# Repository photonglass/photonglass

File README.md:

日本語 | [English](README.en.md)

# PHOTON GLASS

一人称のカメラで捉えるイメージから，音などのフィードバックでユーザーにインタラクションする，メガネ型のデバイス〈PHOTON GLASS〉のハードウェアデータです。
PHOTON GLASS は、文字を読み上げるメガネOTON GLASS ver5 を元にしながら、自作の容易さや改変性を高め、ツールキットとして新しく開発したものです。
基板2枚（メイン基板・カメラ基板）の設計データ、3Dプリンターで造形できる本体とカメラユニットの筐体、電源ケーブルのカバー、本体のプログラム、組み立てとセットアップの手順を公開しています。
ここで公開しているプログラムは、PHOTON GLASS のサンプル実装のひとつです。一人称カメラで捉えた文字を読み上げる（画像から文字を認識し、音声で読み上げる）機能を実行します。

## 中身

| フォルダ | 内容 | 開けるソフト |
|---|---|---|
| [`hardware/`](hardware/README.md) | 基板2枚の概要、ファイルの開き方、元設計からの変更 | — |
| [`hardware/main-board/`](hardware/main-board) | メイン基板（Raspberry Pi Zero 2 W に載る音声・ボタン基板） | KiCad 9 以降 / Fusion（Eagle形式） |
| [`hardware/camera-board/`](hardware/camera-board) | カメラ基板（HDMIケーブルでメイン基板とつながる） | KiCad 9 以降 / Fusion（Eagle形式） |
| [`enclosure/main-body/`](enclosure/main-body) | 本体の筐体（ボディ前面・背面・側面、メインボタン、サブボタン、状態ランプのレンズ） | F3D（Fusion）/ STEP（FreeCAD など）/ STL・3MF（スライサー） |
| [`enclosure/camera-unit/`](enclosure/camera-unit) | カメラユニットの筐体・メガネ用アタッチメント | STEP（Fusion・FreeCAD など）/ STL・3MF（スライサー）/ Python（CadQuery） |
| [`enclosure/usb-power-cable/`](enclosure/usb-power-cable) | モバイルバッテリーからメイン基板へ給電するケーブルの作り方（配線・部品）と、USB プラグのカバー | STEP / STL / Python（CadQuery） |
| [`software/`](software) | 本体プログラムと効果音。普段使うのは `main_async.py`、仕組みを学ぶなら流れの読みやすい `main_seq.py`（違いは [`software/README.md`](software/README.md)） | Python 3（Raspberry Pi） |
| [`software/test/`](software/test) | 組み立て後の動作テスト用スクリプト（Raspberry Pi で実行） | Python 3 |
| [`docs/`](docs) | 組み立てガイド（[`BUILD_GUIDE.md`](docs/BUILD_GUIDE.md)）、Raspberry Pi のセットアップ（[`SETUP_RASPBERRY_PI.md`](docs/SETUP_RASPBERRY_PI.md)）、部品リスト（[`parts_list.md`](docs/parts_list.md)：データシート・回路記号の照合結果） | — |

## はじめての人へ
- **まず読む**：[`docs/BUILD_GUIDE.md`](docs/BUILD_GUIDE.md) に、発注から動かすまでの作業の順番と、それぞれで読むドキュメントをまとめています。
- **基板を作る**：[`hardware/JLCPCB_ORDERING.md`](hardware/JLCPCB_ORDERING.md) の手順で、JLCPCB に部品実装まで発注できます（ガーバー・部品表・部品配置ファイル付き）。
- **筐体を印刷する**：本体は [`enclosure/main-body/README.md`](enclosure/main-body/README.md)、カメラユニットは [`enclosure/camera-unit/README.md`](enclosure/camera-unit/README.md) に、印刷設定（Bambu Lab A1 / PETG）と組み立て手順があります。
- **Raspberry Pi を準備する**：[`docs/SETUP_RASPBERRY_PI.md`](docs/SETUP_RASPBERRY_PI.md) に、OS の書き込みから動作テスト、自動起動までの手順があります。
- **設計を変える**：基板は KiCad か Fusion で、筐体は STEP を CAD に読み込んで編集します（本体は Fusion の元データ `.f3d` もあります。カメラユニットと電源ケーブルのカバーは、`src/` の Python スクリプトの数値を変えて作り直すこともできます）。

## 質問・不具合の報告

質問や不具合の報告は、GitHub の Issues で受け付けています。
https://github.com/photonglass/photonglass/issues

## 憲法
PHOTON GLASS の理念と利用、名称、特許については、[憲法（`CHARTER.md`）](CHARTER.md)に定めています。

## ライセンス
Copyright (C) 株式会社オトングラス

対象ごとに、次のライセンスで公開しています。

| 対象 | 含まれるもの | ライセンス | 全文 |
|---|---|---|---|
| ソフトウェア | `software/` のプログラム（`main_async.py`・`main_seq.py`・`test/` など） | GNU General Public License v3.0（GPL-3.0-only） | [`LICENSE`](LICENSE) |
| ハードウェア | `hardware/`（基板の KiCad・Eagle データ、BOM・CPL、ガーバーを作るスクリプト `hardware/tools/gerbgen.py`）、`enclosure/`（筐体の CadQuery スクリプトと設計データ。本体の Fusion の元データ `.f3d` を含む）と、それらの生成物（ガーバー、STL・STEP・3MF）。**例外**：README・写真・画像と `hardware/JLCPCB_ORDERING.md` は除く（ドキュメント・写真・画像として CC BY-SA 4.0） | CERN Open Hardware Licence Version 2 - Strongly Reciprocal（CERN-OHL-S v2） | [`LICENSE-HARDWARE`](LICENSE-HARDWARE) |
| ドキュメント・写真・画像 | `docs/`、`CHARTER.md`、`CONTRIBUTING.md`、各フォルダの `README.md`、`hardware/JLCPCB_ORDERING.md`、Issue のテンプレート（`.github/ISSUE_TEMPLATE/`）、写真・画像（各フォルダの `images/` など） | クリエイティブ・コモンズ 表示-継承 4.0 国際（CC BY-SA 4.0） | 公式テキスト：[日本語](https://creativecommons.org/licenses/by-sa/4.0/legalcode.ja)・[English](https://creativecommons.org/licenses/by-sa/4.0/legalcode.en) |
| サウンド | `software/sound/` の効果音 | CC BY-SA 4.0 | 同上 |

- 各 README、写真・画像、`hardware/JLCPCB_ORDERING.md` は、`hardware/`・`enclosure/`・`software/` の中にあっても CC BY-SA 4.0 です。`software/sound/` も、`software/` の中にありますが CC BY-SA 4.0 です。
- 文書の英語版（`README.en.md`・`CHARTER.en.md`・`hardware/JLCPCB_ORDERING.en.md` など、名前の末尾が `.en.md` のファイル）も、日本語版と同じく CC BY-SA 4.0 です。

### CC BY-SA 4.0 のクレジット表記
ドキュメント・写真・画像・サウンドは、株式会社オトングラスが CC BY-SA 4.0 で提供しています。全文のファイルはこのリポジトリに入れていないので、公式テキスト（[日本語](https://creativecommons.org/licenses/by-sa/4.0/legalcode.ja)・[English](https://creativecommons.org/licenses/by-sa/4.0/legalcode.en)）を見てください。

使うときは、次のようにクレジットを表記してください。改変したときは、改変したことも書いてください。
```
PHOTON GLASS（Copyright (C) 株式会社オトングラス）
https://github.com/photonglass/photonglass
CC BY-SA 4.0 https://creativecommons.org/licenses/by-sa/4.0/
```

### かんたんな説明
正確な条件は、各ライセンスの全文を見てください。

**できること**
- 誰でも無料で、このデータで基板や筐体を作り、使い、売ることができます。
- 自由に改変できます。

**守ること**
- 作ったもの・改変したものを人に配ったり売ったりするときは、元と同じライセンスで公開する。
  - ソフトウェアとハードウェアは、受け取った人がソース（プログラム・設計データ）を手に入れられるようにする。ハードウェアの場合は、ソースを渡すか、ソースの置き場所を知らせる。
- 著作権表示とライセンスの表示を消さない。改変した場合は、いつ・どこを変えたかを書く。
- ドキュメント・写真・画像・サウンドを使うときは、上のクレジットを表記する。

**その他**
- 無保証です（作ったものが動かなくても、作者は責任を負いません）。
- 自分で使うだけなら、改変したデータを公開する義務はありません。
- 特許の扱いは、憲法の[「3. 特許について」](CHARTER.md#3-特許について)を見てください。

### 商用ライセンス
クローズドな製品への組み込みなど、各ライセンスの条件と異なる利用を希望する場合は、商用ライセンスを個別に契約できます。問い合わせはこちら：https://note.com/keisukeshimakage/n/nef3c9957ae25

### 含まれていないもの
- 部品メーカーや EasyEDA/LCSC が配布している部品の3Dモデル（再配布の条件がはっきりしないため）。基板の3D形状は KiCad や Fusion の3Dビューで確認してください。
- Google Cloud の API キー（各自で用意して、プログラムと同じフォルダの `api_key.txt` に書く。書き方は [`software/README.md`](software/README.md#動かし方)）。

### クレジット
**PHOTON GLASS（2026年）**
- 回路・基板設計、ドキュメンテーション：山中将治（Masaharu Yamanaka）
- プロダクトデザイン：小松靖知（Yasutomo Komatsu）
- プログラミング：石塚日向（Hinata Ishizuka）
- アドバイジング：須田拓也（Hiroya Suda）、高橋卓久真（Takuma Takahashi）、陳冠宇（Chen Kuan-Yu）

**OTON GLASS ver5（2019年）― PHOTON GLASSの元となったモデル**
- エンジニアリング：宮下恵太（Keita Miyashita）
- サーバーサイドエンジニアリング：鶴岡秀樹（Hideki Tsuruoka）
- プロダクトデザイン：佐野友優（Tomomasa Sano）
- サウンドデザイン：田中堅大（Kenta Tanaka）

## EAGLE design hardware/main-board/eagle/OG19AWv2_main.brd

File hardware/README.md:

日本語 | [English](README.en.md)

# 基板 / Boards

| 基板 | 役割 | 大きさ |
|---|---|---|
| [`main-board/`](main-board) OG19AWv2 | Raspberry Pi Zero 2 W の40ピンに挿す。音声出力（PCM5102A + PAM8304）、スピーカー用コネクタ、ボタン4個、RGB LED、ヘッドホンジャック、電源用コネクタ（5V）、カメラ基板へのHDMI | 79 × 42 mm、2層 |
| [`camera-board/`](camera-board) OG19 PC-3 | カメラユニットの中の基板。カメラ（Adafruit 3508 Zero Spy Camera、標準レンズ版。[`enclosure/camera-unit` の「必要な部品」](../enclosure/camera-unit/README.md#必要な部品)）をつなぎ、カメラボタン（シャッター）とLEDを載せる。HDMIケーブルでメイン基板へ | 39.3 × 17.2 mm、2層 |

## ファイルの開き方
| ソフト | 開くファイル | 方法 |
|---|---|---|
| **KiCad 9 以降** | `kicad/*.kicad_pro` | ダブルクリックで開く。KiCad 10 で開いて保存すると、ファイルが新しい形式になり KiCad 9 では開けなくなる |
| **Fusion**（旧 Eagle） | `eagle/*.sch` / `*.brd` | Fusion の「ファイル → 開く」で `.sch` を選ぶと、回路図と基板がセットで電子設計として開く |
| Eagle 9.x | `eagle/*.sch` / `*.brd` | そのまま開く（Eagle は 2026年6月に販売とサポートが終了しているので、これから使うなら KiCad か Fusion） |

Eagle・KiCad の部品ライブラリのうち、jst-xh（メイン基板の `5V`・`SPK` のコネクタ）は、yuhki50 氏の [eagle-pcb-library](https://github.com/yuhki50/eagle-pcb-library)（MIT ライセンス）に由来します。

## JLCPCB で作る
各基板のフォルダに、発注に必要なファイル（ガーバー・BOM・CPL）がそろっています。
発注の手順は **[`JLCPCB_ORDERING.md`](JLCPCB_ORDERING.md)** を見てください（基板製造の設定、部品実装の設定、部品の向きの確認、手はんだで付ける部品）。

スピーカー用コネクタの向きは [`main-board/images/speaker_connector_orientation.png`](main-board/images/speaker_connector_orientation.png) を見てください。

## 元設計（OTON GLASS ver5）からの変更
- 在庫のない部品を JLCPCB で買える部品に置き換え（ヘッドホンジャック、RGB LED、ピンソケット、抵抗値の近似など）。詳しくは [`docs/parts_list.md`](../docs/parts_list.md)。
- メイン基板：上辺の段差をなくした、左右の角を対称な面取りにした、HDMI とヘッドホンジャックの前面をそろえた、ボタンを基板の端まで出した、不足していたビアを追加した、など。
- **RGB LED の色と GPIO の対応が変わっています**：GPIO9 = 赤、GPIO11 = 緑、GPIO10 = 青。

## 版の履歴
| 版（シルクの表記） | 変更 |
|---|---|
| メイン基板 `2026 / PB-4`、カメラ基板 `2026 / PC-4` | シルクの名前を「PHOTON GLASS」に変更（前の版はメイン基板「OTONGLASS」、カメラ基板「OTON GLASS」）。メイン基板の表面に、リポジトリの URL（`github.com/photonglass/photonglass`）とライセンス（`CERN-OHL-S v2`）を追加（2026-11-25 に、この文字と「PHOTON GLASS / 2026 / PB-4」を高さ 1.0 mm・線の太さ 0.16 mm に拡大。JLCPCB の最小値は高さ 1.0 mm・線の太さ 0.153 mm）。**銅箔・穴・レジスト・メタルマスク・外形は前の版と同じ**で、変わったのは表面のシルク（`.GTO`）だけ。設計データに残っていた、手はんだ部品（VR1・SW_MAIN・SW_SUB／UP／DOWN）の旧部品の LCSC 番号を外し、実際に使う部品の型番（`MPN`）と購入先（`SUPPLIER`）に置き換え |
| メイン基板 `2019 / PB-3`、カメラ基板 `2019 / PC-3` | 元設計を JLCPCB 向けに直した最初の版（上の「元設計からの変更」） |

カメラ基板は小さく、裏面にも GND のビアが並んでいて URL を入れる場所がないため、URL とライセンスはメイン基板にだけ入れています。

## 組み立て後のテスト
[`software/test/hw_test.py`](../software/test/hw_test.py) を Raspberry Pi で実行すると、LED → ボタン → スピーカー → カメラの順に確認できます。
Raspberry Pi の準備とテストの実行方法は [`docs/SETUP_RASPBERRY_PI.md`](../docs/SETUP_RASPBERRY_PI.md) にあります。

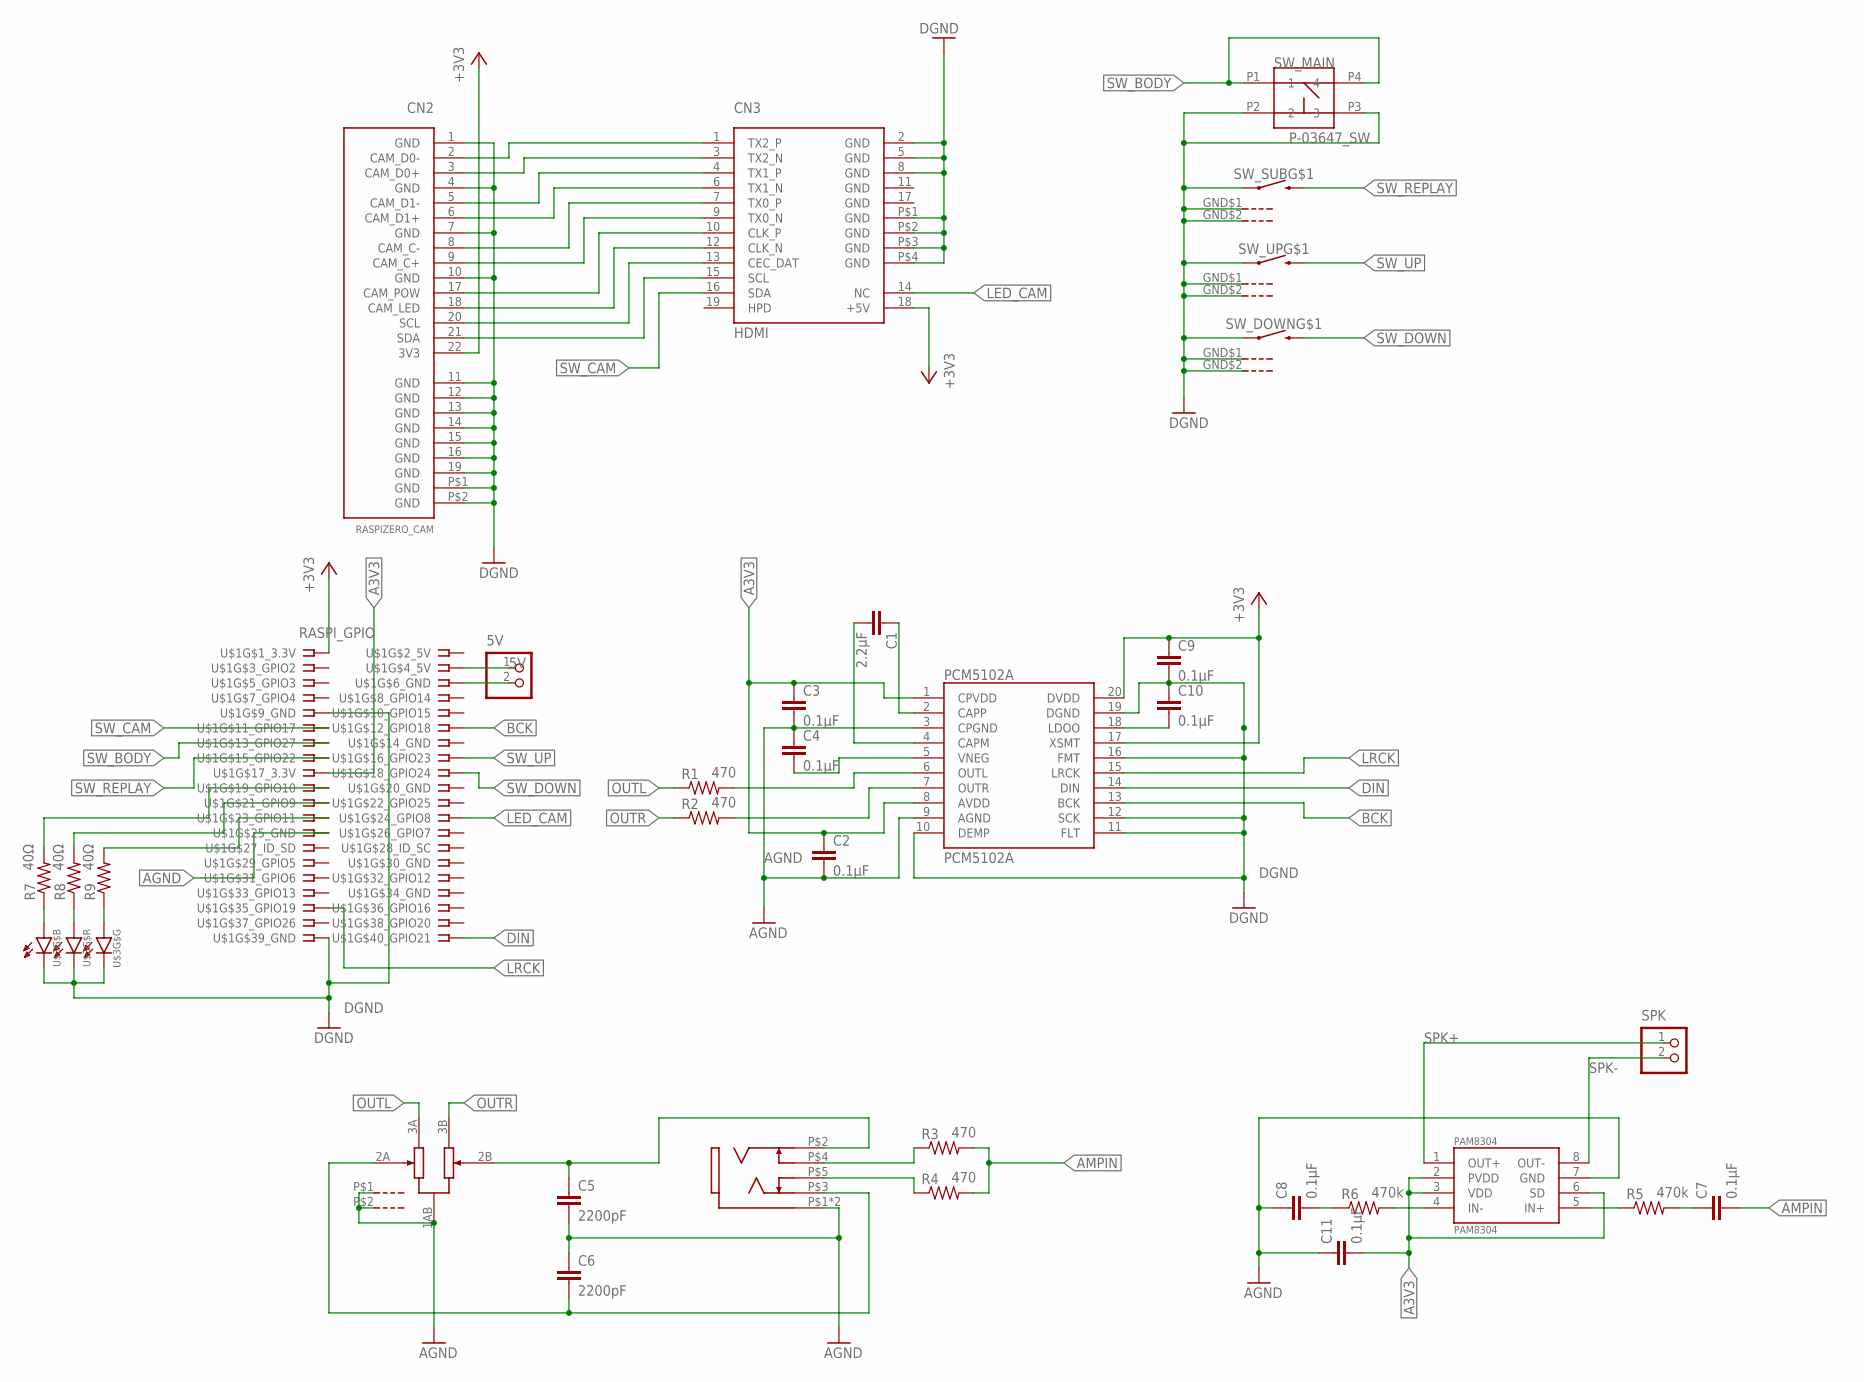
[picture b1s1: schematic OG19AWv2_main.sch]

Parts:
5V: S2B-XH-A; B2B-XH-A; LCSC C158012
C1: 2.2μF; C0603; LCSC C23630
C2, C3, C4, C7, C8, C9, C10, C11: 0.1μF; C0603; LCSC C14663
C5, C6: 2200pF; C0603; LCSC C1604
CN1: SWICHCRAFT_3.5MM_PHONE_JACK; SJ-43516-SMT; LCSC C4992780
CN2: RASPIZERO_CAM; FH12-22S-0.5SH; LCSC C597981
CN3: HDMI; LCSC C427307
PAM8304: PAM8304; MSOP8; LCSC C581342
PCM5102A: PCM5102A; SSOP20; LCSC C107671
R1, R2, R3, R4: 470; R0603; LCSC C23179
R5, R6: 470k; R0603; LCSC C23178
R7, R8, R9: 40Ω; R0603; LCSC C23047
SPK: S2B-XH-A; B2B-XH-A; LCSC C158012
SW_DOWN: ALPS_SKHH_TACT_SWITCH; SKHH_SIDEPUSH; MPN Alps SKHHLPA010
SW_MAIN: P-03647_SW; SW; MPN Cosland TS-0606-F-N-RED
SW_SUB: ALPS_SKHH_TACT_SWITCH; SKHH_SIDEPUSH; MPN Alps SKHHLPA010
SW_UP: ALPS_SKHH_TACT_SWITCH; SKHH_SIDEPUSH; MPN Alps SKHHLPA010
U$1: RASPI_GPIO; SSW-120-02-G-D; LCSC C5124634
U$3: KPF-3236SURKMGKPBC; S6-3528RGBTA; LCSC C2843672
VR1: ALPS_RK10J; RK10J_DIP; MPN R1001G16T2B-B10K

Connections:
5V: 5V.1, U$1.4
+3V3: C9.1, CN2.22 (3V3), CN3.18 (+5V), PCM5102A.17 (XSMT), PCM5102A.20 (DVDD), U$1.1
A3V3: C2.1, C3.1, C11.2, PAM8304.2 (PVDD), PAM8304.3 (VDD), PAM8304.6 (SD), PCM5102A.1 (CPVDD), PCM5102A.8 (AVDD), U$1.17
AGND: C2.2, C3.2, C4.1, C5.2, C6.1, C8.1, C11.1, CN1.P$1, CN1.P$6, PAM8304.7 (GND), PCM5102A.3 (CPGND), PCM5102A.9 (AGND), U$1.25, VR1.1AB, VR1.P$1 (G), VR1.P$2 (G)
AMPIN: C7.2, R3.2, R4.2
BCK: PCM5102A.13 (BCK), U$1.12
DGND: C9.2, C10.1, CN2.1 (GND), CN2.4 (GND), CN2.7 (GND), CN2.10 (GND), CN2.11 (GND), CN2.12 (GND), CN2.13 (GND), CN2.14 (GND), CN2.15 (GND), CN2.16 (GND), CN2.19 (GND), CN2.P$1 (GND), CN2.P$2 (GND), CN3.2 (GND), CN3.5 (GND), CN3.8 (GND), CN3.P$1 (GND), CN3.P$2 (GND), CN3.P$3 (GND), CN3.P$4 (GND), PCM5102A.10 (DEMP), PCM5102A.11 (FLT), PCM5102A.12 (SCK), PCM5102A.16 (FMT), PCM5102A.19 (DGND), SW_DOWN.GND$1 (G), SW_DOWN.GND$2 (G), SW_DOWN.P$1 (1), SW_MAIN.P2 (2), SW_MAIN.P3 (3), SW_SUB.GND$1 (G), SW_SUB.GND$2 (G), SW_SUB.P$1 (1), SW_UP.GND$1 (G), SW_UP.GND$2 (G), SW_UP.P$1 (1), U$1.9, U$1.39, U$3.P$1 (K), U$3.P$2 (K), U$3.P$3 (K)
DIN: PCM5102A.14 (DIN), U$1.40
LED_CAM: CN3.14 (NC), U$1.24
LRCK: PCM5102A.15 (LRCK), U$1.35
unnamed: C5.1, CN1.P$2, VR1.2B
unnamed: C6.2, CN1.P$3, VR1.2A
unnamed: CN1.P$4, R3.1
unnamed: C1.1, PCM5102A.2 (CAPP)
unnamed: C10.2, PCM5102A.18 (LDOO)
unnamed: C1.2, PCM5102A.4 (CAPM)
unnamed: C4.2, PCM5102A.5 (VNEG)
unnamed: CN1.P$5, R4.1
unnamed: PAM8304.5 (IN+), R5.1
unnamed: C7.1, R5.2
unnamed: PAM8304.4 (IN-), R6.2
unnamed: CN2.2 (CAM_D0-), CN3.1 (TX2_P)
unnamed: C8.2, R6.1
unnamed: CN2.3 (CAM_D0+), CN3.3 (TX2_N)
unnamed: CN2.5 (CAM_D1-), CN3.4 (TX1_P)
unnamed: CN2.6 (CAM_D1+), CN3.6 (TX1_N)
unnamed: CN2.8 (CAM_C-), CN3.7 (TX0_P)
unnamed: CN2.9 (CAM_C+), CN3.9 (TX0_N)
unnamed: CN2.17 (CAM_POW), CN3.10 (CLK_P)
unnamed: CN2.18 (CAM_LED), CN3.12 (CLK_N)
unnamed: CN2.20 (SCL), CN3.13 (CEC_DAT)
unnamed: CN2.21 (SDA), CN3.15 (SCL)
unnamed: R7.1, U$3.P$4 (A)
unnamed: 5V.2, U$1.6
unnamed: R7.2, U$1.19
unnamed: R8.2, U$1.21
unnamed: R9.2, U$1.23
unnamed: R8.1, U$3.P$5 (A)
unnamed: R9.1, U$3.P$6 (A)
OUTL: R1.1, VR1.3A
OUTL1: PCM5102A.6 (OUTL), R1.2
OUTR: R2.1, VR1.3B
OUTR1: PCM5102A.7 (OUTR), R2.2
SPK+: PAM8304.1 (OUT+), SPK.1
SPK-: PAM8304.8 (OUT-), SPK.2
SW_BODY: SW_MAIN.P1 (1), SW_MAIN.P4 (4), U$1.13
SW_CAM: CN3.16 (SDA), U$1.11
SW_DOWN: SW_DOWN.P$2 (2), U$1.18
SW_REPLAY: SW_SUB.P$2 (2), U$1.15
SW_UP: SW_UP.P$2 (2), U$1.16

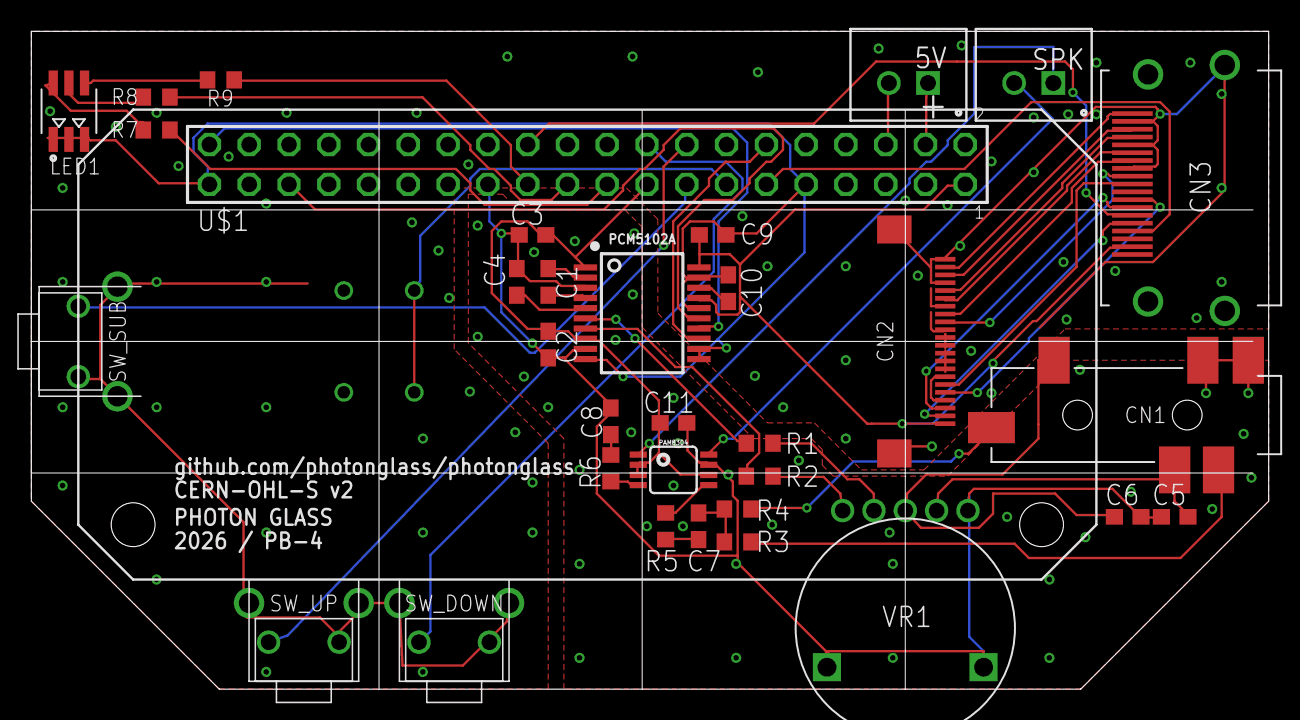
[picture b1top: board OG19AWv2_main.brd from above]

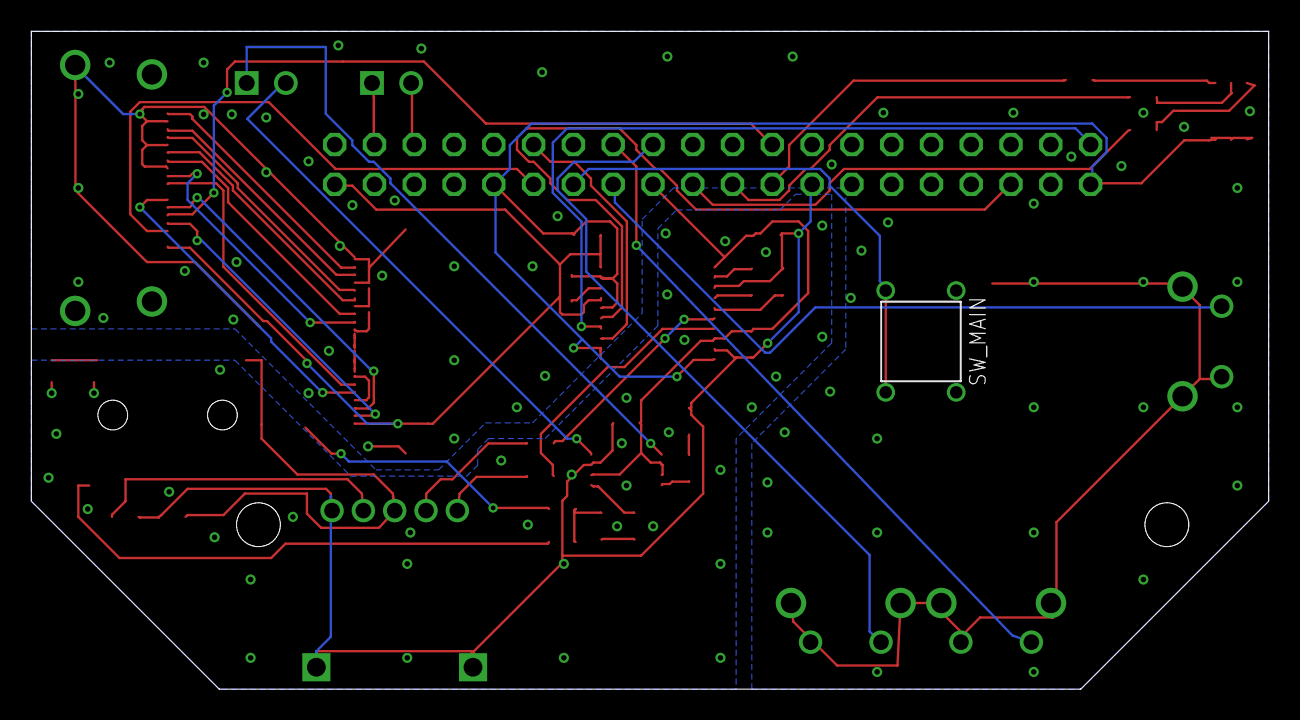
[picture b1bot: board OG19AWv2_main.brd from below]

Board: 2 copper layers, 79.0 x 42.0 mm, 34 parts (2 on the bottom side), 50 nets.

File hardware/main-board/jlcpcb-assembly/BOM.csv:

Comment,Designator,Footprint,JLCPCB Part #（optional）,Manufacturer Part,Library Type,Stock (checked 2026-10-14),Note
2.2μF,C1,0603,C23630,Samsung Electro-Mechanics CL10A225KO8NNNC,Basic,3391639,
2200pF,"C5,C6",0603,C1604,FH (Guangdong Fenghua Advanced Tech) 0603B222K500NT,Basic,982010,X7R。音質重視なら C0G の C33353 (Extended) に変更可
0.1μF,"C10,C11,C2,C3,C4,C7,C8,C9",0603,C14663,YAGEO CC0603KRX7R9BB104,Basic,40021582,
SWICHCRAFT_3.5MM_PHONE_JACK,CN1,SMD,C4992780,CUI SJ-43516-SMT-TR,Extended,136,代替: 元 Switchcraft 35RASMT4BHNTRX (在庫0)。フットプリント変更・配線修正済み
RASPIZERO_CAM,CN2,"SMD,P=0.5mm,Surface Mount，Right Angle",C597981,HRS(Hirose) FH12-22S-0.5SH(55),Extended,640,
HDMI,CN3,SMD,C427307,Amphenol ICC 10029449-111RLF,Extended,1503,元部品と同系列 (Amphenol 10029449)
PAM8304,PAM8304,MSOP-8,C581342,Diodes Incorporated PAM8304ASR,Extended,2644,PAM8304ASR = MSOP-8 (ピン配置一致確認済み)
PCM5102A,PCM5102A,TSSOP-20,C107671,Texas Instruments PCM5102APWR,Extended,3701,
470,"R1,R2,R3,R4",0603,C23179,UNI-ROYAL(Uniroyal Elec) 0603WAF4700T5E,Basic,5483823,
470k,"R5,R6",0603,C23178,UNI-ROYAL(Uniroyal Elec) 0603WAF4703T5E,Basic,1243118,
40Ω,"R7,R8,R9",0603,C23047,UNI-ROYAL(Uniroyal Elec) 0603WAF402JT5E,Extended,23804,40Ω 指定。40Ω ちょうどの在庫品がないため 40.2Ω ±1%（差 0.5%、部品の許容差内）
RASPI_GPIO,U$1,"Plugin,P=2.54mm",C5124634,BOOMELE(Boom Precision Elec) 2.54-2*20P,Extended,8609,代替: 元 Samtec SSW-120-02-G-D (在庫5・高価)。汎用2x20ピンソケット 8.5mm
KPF-3236SURKMGKPBC,U$3,SMD3528-6P,C2843672,TUOZHAN S6-3528RGBTA,Extended,6388,代替: 元 Kingbright KPF-3236SURKMGKPBC (JLC未登録)。フットプリント変更、色の割当が変化

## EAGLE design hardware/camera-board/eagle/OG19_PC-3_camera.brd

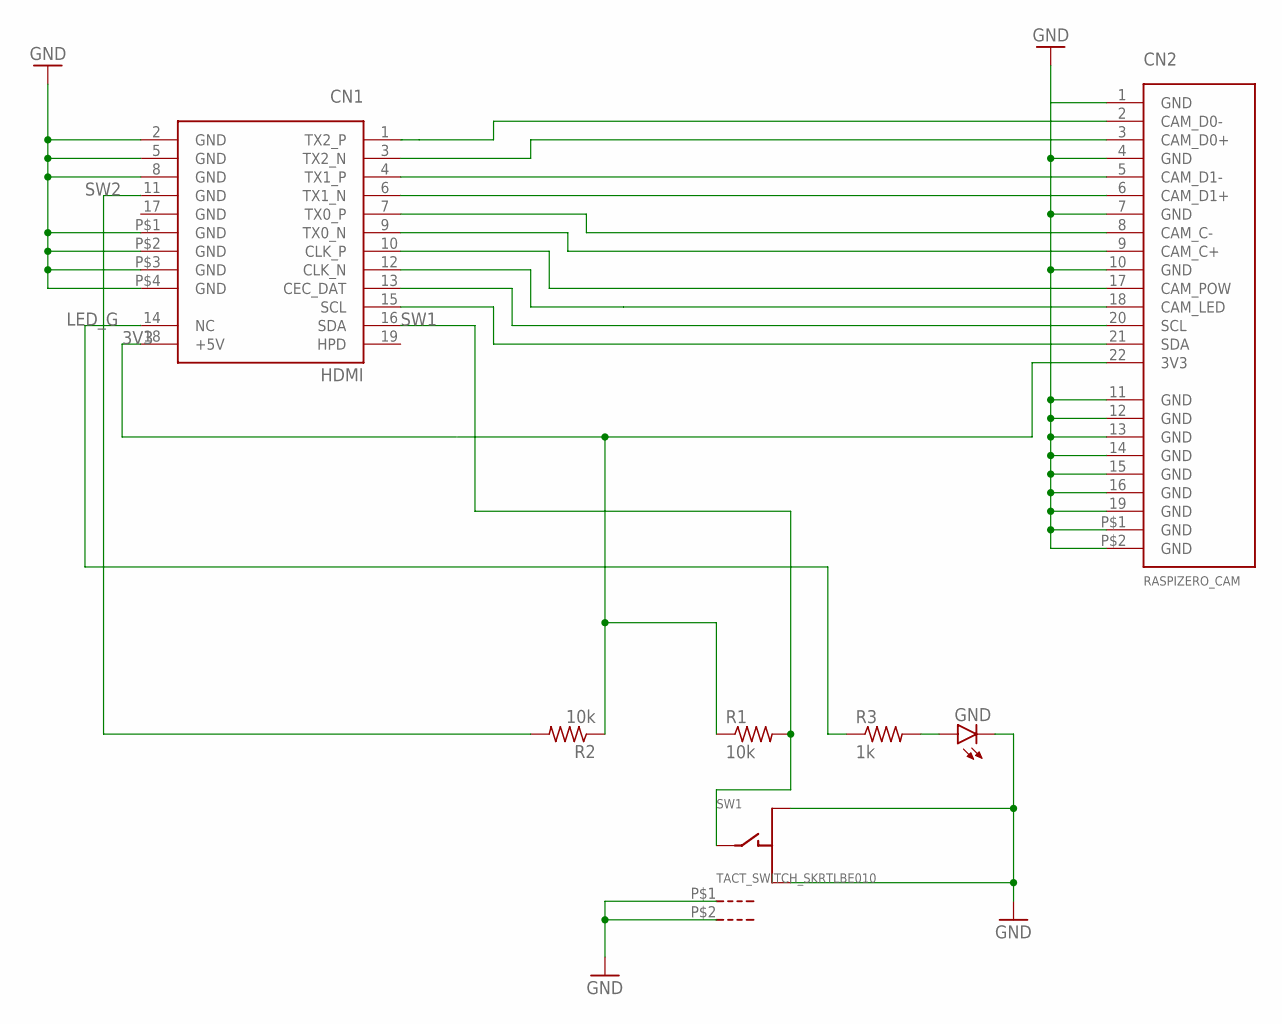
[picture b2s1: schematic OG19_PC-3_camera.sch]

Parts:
CN1: HDMI; LCSC C427307
CN2: RASPIZERO_CAM; FH12-22S-0.5SH; LCSC C597981
GND: LEDCHIPLED_0603; CHIPLED_0603; LCSC C2286
R1, R2: 10k; R0603; LCSC C25804
R3: 1k; R0603; LCSC C21190
SW1: TACT_SWITCH_SKRTLBE010; SKRTLBE010; LCSC C127481

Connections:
3V3: CN1.18 (+5V), CN2.22 (3V3), R1.1, R2.1
GND: CN1.2 (GND), CN1.5 (GND), CN1.8 (GND), CN1.P$1 (GND), CN1.P$2 (GND), CN1.P$3 (GND), CN1.P$4 (GND), CN2.1 (GND), CN2.4 (GND), CN2.7 (GND), CN2.10 (GND), CN2.11 (GND), CN2.12 (GND), CN2.13 (GND), CN2.14 (GND), CN2.15 (GND), CN2.16 (GND), CN2.19 (GND), CN2.P$1 (GND), CN2.P$2 (GND), GND.C, SW1.P$1 (G), SW1.P$2 (G), SW1.P$3 (1), SW1.P$5 (3)
LED_G: CN1.14 (NC), R3.1
unnamed: CN1.1 (TX2_P), CN2.2 (CAM_D0-)
unnamed: CN1.10 (CLK_P), CN2.17 (CAM_POW)
unnamed: CN1.3 (TX2_N), CN2.3 (CAM_D0+)
unnamed: CN1.4 (TX1_P), CN2.5 (CAM_D1-)
unnamed: CN1.6 (TX1_N), CN2.6 (CAM_D1+)
unnamed: CN1.13 (CEC_DAT), CN2.20 (SCL)
unnamed: CN1.15 (SCL), CN2.21 (SDA)
unnamed: CN1.12 (CLK_N), CN2.18 (CAM_LED)
unnamed: GND.A, R3.2
unnamed: CN1.7 (TX0_P), CN2.8 (CAM_C-)
unnamed: CN1.9 (TX0_N), CN2.9 (CAM_C+)
SW1: CN1.16 (SDA), R1.2, SW1.P$4 (2)
SW2: CN1.11 (GND), R2.2

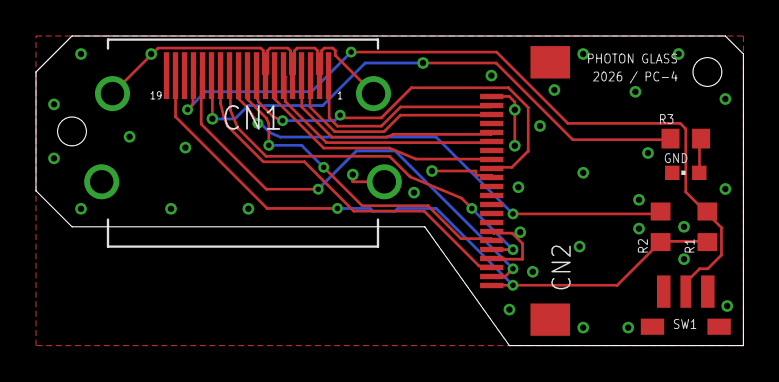
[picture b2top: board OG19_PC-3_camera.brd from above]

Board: 2 copper layers, 39.3 x 17.2 mm, 7 parts (0 on the bottom side), 16 nets.

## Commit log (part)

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2026-06-25 はじめに公開するファイルたち
